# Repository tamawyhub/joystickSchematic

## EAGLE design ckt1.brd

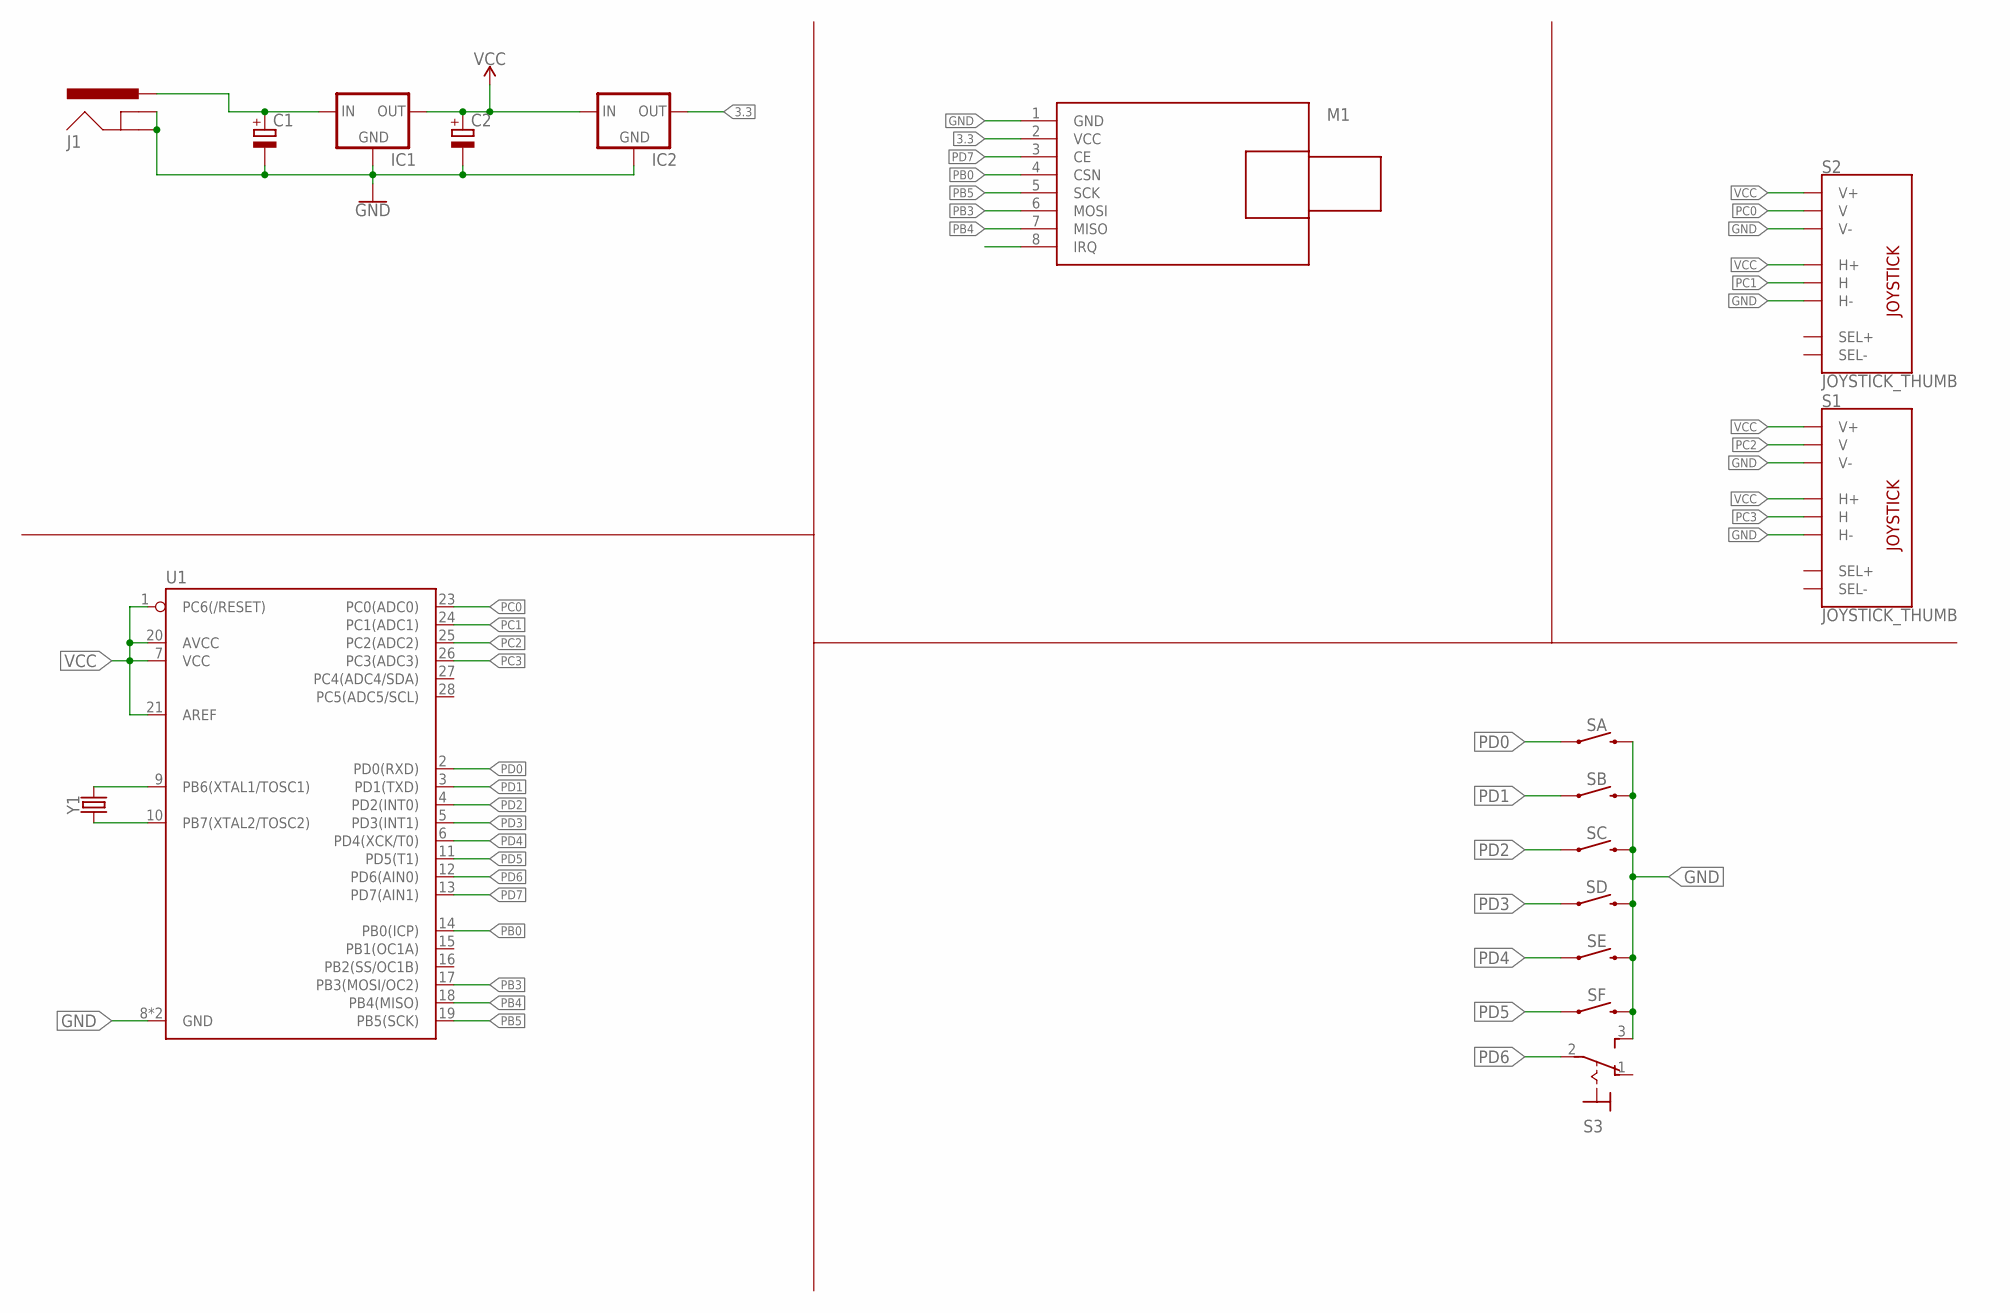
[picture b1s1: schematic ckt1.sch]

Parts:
C1, C2: CPOL-EUE2-5; E2-5
IC1, IC2: 78XXS
J1: POWER_JACKSLT; POWER_JACK_SLOT
M1: WIRELESS-NRF24L01-PA-EXT
S1, S2: JOYSTICK_THUMB; JOYSTICK
S3: 320-916
SA: MOMENTARY-SWITCH-SPST-PTH-6.0MM; TACTILE_SWITCH_PTH_6.0MM
SB: MOMENTARY-SWITCH-SPST-PTH-6.0MM; TACTILE_SWITCH_PTH_6.0MM
SC: MOMENTARY-SWITCH-SPST-PTH-6.0MM; TACTILE_SWITCH_PTH_6.0MM
SD: MOMENTARY-SWITCH-SPST-PTH-6.0MM; TACTILE_SWITCH_PTH_6.0MM
SE: MOMENTARY-SWITCH-SPST-PTH-6.0MM; TACTILE_SWITCH_PTH_6.0MM
SF: MOMENTARY-SWITCH-SPST-PTH-6.0MM; TACTILE_SWITCH_PTH_6.0MM
U1: 328P; DIP28
Y1: CRYSTALPTH-HC49US; HC49US

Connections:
3.3: IC2.OUT, M1.2 (VCC)
GND: C1.-, C2.-, IC1.GND, IC2.GND, J1.GND@1 (GNDBREAK), J1.GND@2 (GND), M1.1 (GND), S1.H3 (H-), S1.V3 (V-), S2.H3 (H-), S2.V3 (V-), S3.3 (S), SA.3 (2), SB.3 (2), SC.3 (2), SD.3 (2), SE.3 (2), SF.3 (2), U1.8 (GND), U1.22 (GND)
unnamed: U1.9 (PB6(XTAL1/TOSC1)), Y1.2
unnamed: C1.+, IC1.IN, J1.PWR
unnamed: U1.10 (PB7(XTAL2/TOSC2)), Y1.1
PB0: M1.4 (CSN), U1.14 (PB0(ICP))
PB3: M1.6 (MOSI), U1.17 (PB3(MOSI/OC2))
PB4: M1.7 (MISO), U1.18 (PB4(MISO))
PB5: M1.5 (SCK), U1.19 (PB5(SCK))
PC0: S2.V2 (V), U1.23 (PC0(ADC0))
PC1: S2.H2 (H), U1.24 (PC1(ADC1))
PC2: S1.V2 (V), U1.25 (PC2(ADC2))
PC3: S1.H2 (H), U1.26 (PC3(ADC3))
PD0: SA.1, U1.2 (PD0(RXD))
PD1: SB.1, U1.3 (PD1(TXD))
PD2: SC.1, U1.4 (PD2(INT0))
PD3: SD.1, U1.5 (PD3(INT1))
PD4: SE.1, U1.6 (PD4(XCK/T0))
PD5: SF.1, U1.11 (PD5(T1))
PD6: S3.2, U1.12 (PD6(AIN0))
PD7: M1.3 (CE), U1.13 (PD7(AIN1))
VCC: C2.+, IC1.OUT, IC2.IN, S1.H1 (H+), S1.V1 (V+), S2.H1 (H+), S2.V1 (V+), U1.1 (PC6(/RESET)), U1.7 (VCC), U1.20 (AVCC), U1.21 (AREF)

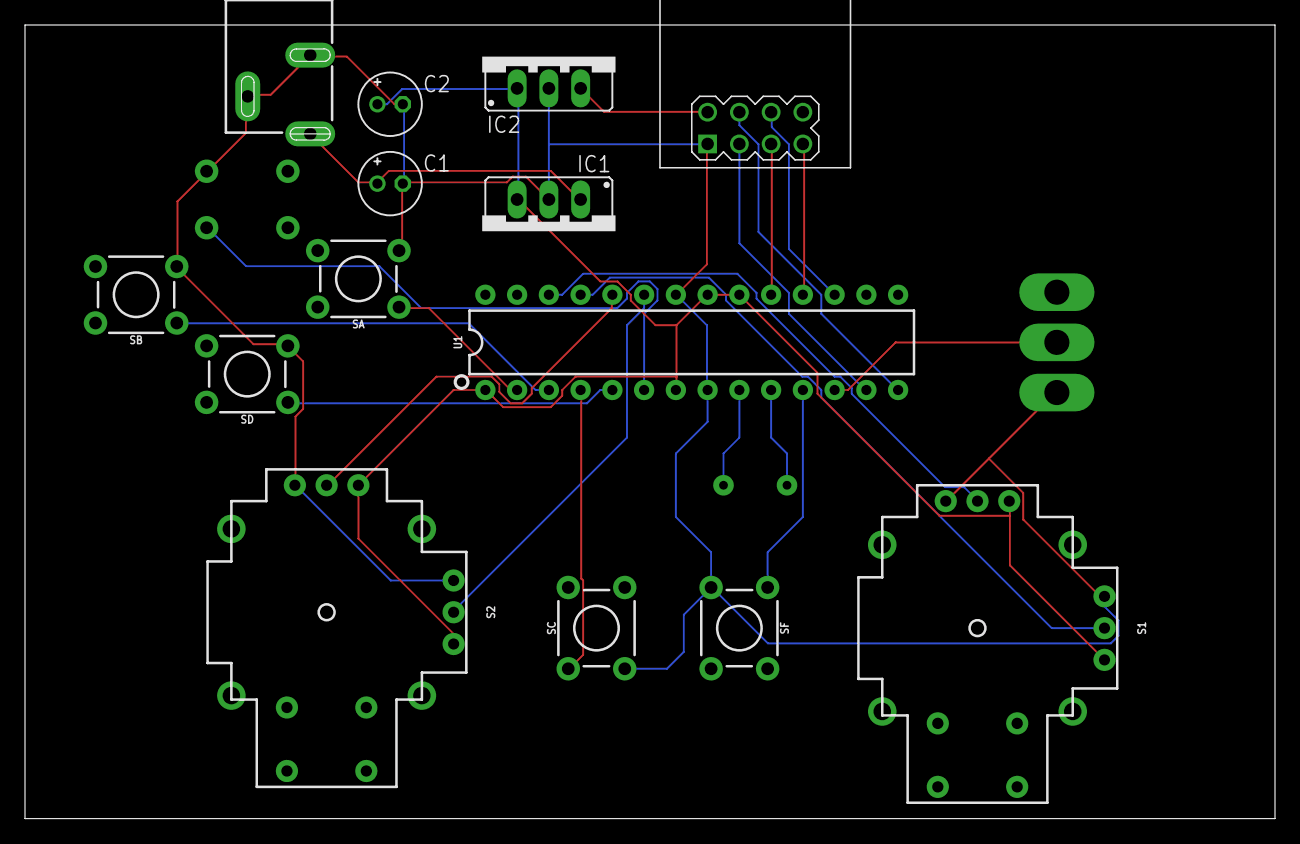
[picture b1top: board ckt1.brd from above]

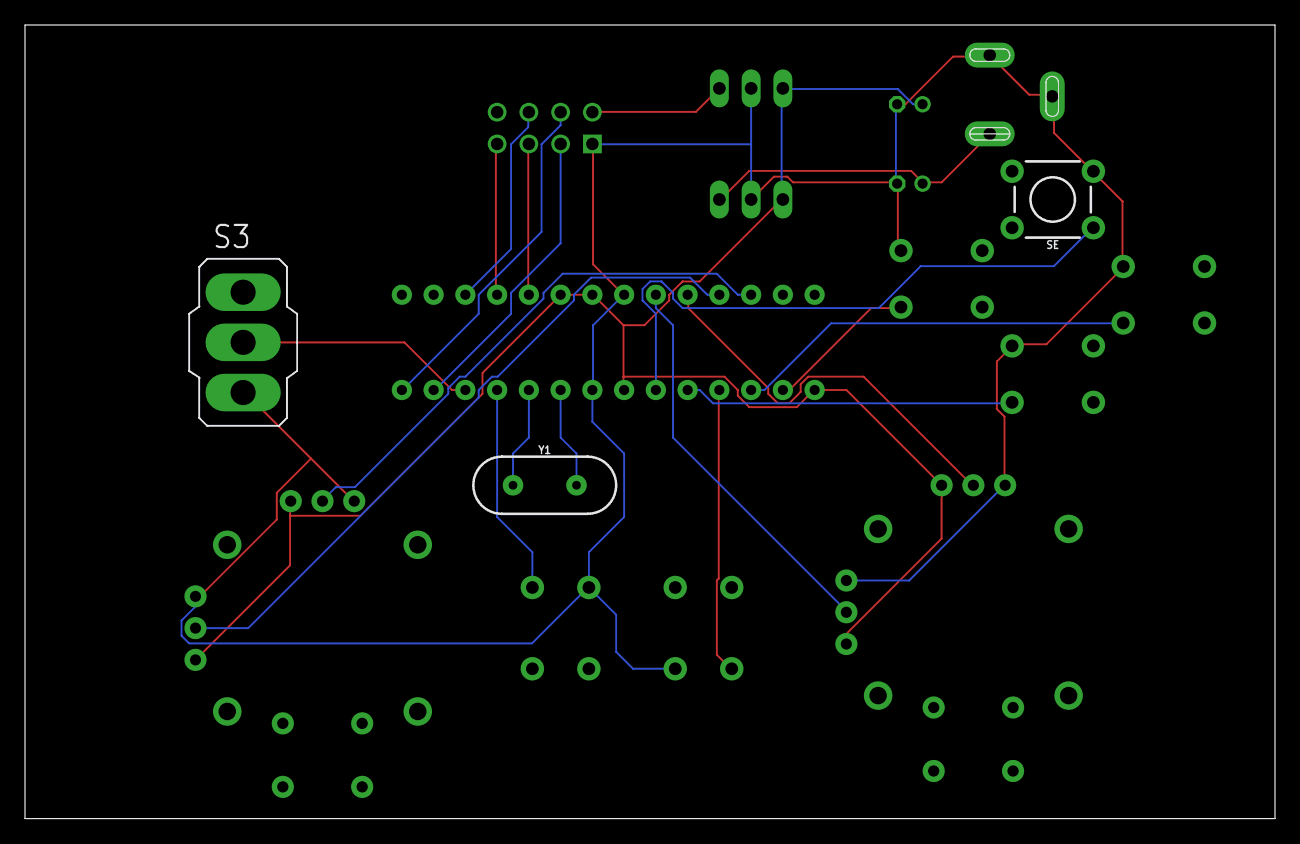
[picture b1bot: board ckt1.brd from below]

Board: 2 copper layers, 100.0 x 63.5 mm, 17 parts (3 on the bottom side), 22 nets.

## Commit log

2019-08-15 Formatting schematic and adding XTAL
2019-08-15 Some changes to the board file

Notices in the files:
parts and their libraries:
SparkFun-Connectors: Licensing: Creative Commons ShareAlike 4.0 International - https://creativecommons.org/licenses/by-sa/4.0
diy-modules: Released under the Creative Commons Attribution 4.0 International License: http://creativecommons.org/licenses/by/4.0
